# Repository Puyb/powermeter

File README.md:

Do It Yourself (DIY) Cycle Power Meter

Based on https://gitlab.com/tbressers/power/ with a custom PCB in the hardware folder

---

Original README:

This is the code for a crank-based power meter, transmitting over BLE to a bike computer. The whole project is based on Steve Jarvis website/gitlab with a nice set of improvements (see gitlab link below) and tested on a 'Adafruit Bluefruit nRF52840 Feather Express' board.

Please find the complete DIY work-instruction here:

https://gitlab.com/tbressers/power/-/wikis/home

Best regards,
Thijs

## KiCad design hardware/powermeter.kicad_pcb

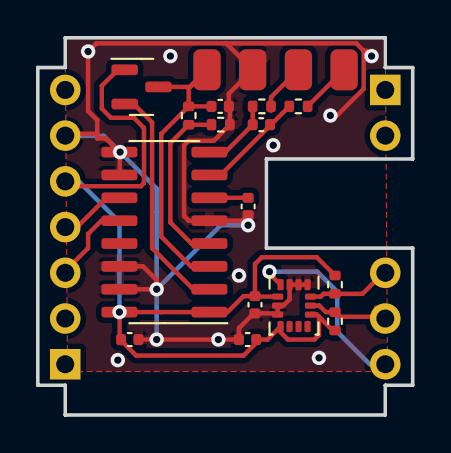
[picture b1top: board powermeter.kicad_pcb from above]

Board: 2 copper layers, 20.8 x 21.0 mm, 19 parts (1 on the bottom side), 20 nets.

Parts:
C1, C2, C5, C6: 0.1uF; C_0402_1005Metric
C3, C4: 10uF; C_0402_1005Metric
J1: Conn_01x04; connecteur
J2, J3: Conn_01x07; PinHeader_1x07_P2.54mm_Vertical
Q1: S8550; SOT-23
R1, R6: 100; R_0402_1005Metric
R2: 20k; R_0402_1005Metric
R3: 8.2k; R_0402_1005Metric
R4, R5: 10k; R_0402_1005Metric
U1: XIAO BLE; MOUDLE16P-SMD-2.54-21X17.8MM
U2: HX711; SOP-16_3.9x9.9mm_P1.27mm
U3: LSM6DS3; LGA-14_3x2.5mm_P0.5mm_LayoutBorder3x4y

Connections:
+3.3V: C3.1, C5.2, C6.1, J3.5, Q1.1 (E), R4.1, R5.1, U1.12 (3v3), U2.1 (VSUP), U2.16 (DVDD), U3.5 (VDDIO), U3.8 (VDD), U3.12 (CS)
/5V: J3.7, U1.14 (5v)
/HX_CLK: J3.4, U1.11 (D10/MOSI), U2.11 (PD_SCK)
/HX_DATA: J3.3, U1.10 (D9/MISO), U2.12 (DOUT)
/MPU_INT: J2.7, U1.7 (D6/TX), U3.4 (INT1)
/SCL: J2.6, R5.2, U1.6 (D5/A5/SCL), U3.13 (SCL)
/SDA: J2.5, R4.2, U1.5 (D4/A4/SDA), U3.14 (SDA)
GND: C2.2, C3.2, C4.2, C5.1, C6.2, J1.2, J3.6, R3.2, U1.13 (GND), U2.5 (AGND), U2.9 (INB-), U2.10 (INB+), U2.14 (XI), U2.15 (RATE), U3.1 (SDO/SA0), U3.2 (SDX), U3.3 (SCX), U3.6 (GND), U3.7 (GND)
unnamed: C4.1, J1.1, Q1.3 (C), R2.1, U2.3 (AVDD)
unnamed: J1.3, R1.2
unnamed: J1.4, R6.2
unnamed: J2.1, U1.1 (D0/A0)
unnamed: J2.2, U1.2 (D1/A1)
unnamed: J3.1, U1.8 (D7/RX)
unnamed: J3.2, U1.9 (D8/SCK)
unnamed: Q1.2 (B), U2.2 (BASE)
unnamed: C1.1, R1.1, U2.8 (INA+)
unnamed: C1.2, R6.1, U2.7 (INA-)
unnamed: C2.1, U2.6 (VBG)
unnamed: R2.2, R3.1, U2.4 (VFB)

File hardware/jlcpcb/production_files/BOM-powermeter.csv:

Comment,Designator,Footprint,LCSC
S8550,Q1,SOT-23,C105432
0.1uF,"C1,C2,C5,C6",C_0402_1005Metric,C1525
10uF,"C3,C4",C_0402_1005Metric,C15525
100,"R1,R6",R_0402_1005Metric,C25076
10k,"R4,R5",R_0402_1005Metric,C25744
20k,R2,R_0402_1005Metric,C25765
8.2k,R3,R_0402_1005Metric,C2906967
HX711,U2,SOP-16_3.9x9.9mm_P1.27mm,C6705483
LSM6DS3,U3,LGA-14_3x2.5mm_P0.5mm_LayoutBorder3x4y,C967633

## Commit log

2021-11-05 Initial commit, copied files from Steve Jarvis and added sleep mode for Feather Express boards https://iamteapot.dev/homemade-power-meter/ https://gitlab.com/sjarvis/powermeter
    TODO:
    - Cleanup code
    - Integrate calibration
    - Many more things!
2021-11-05 Cleanup
2021-11-12 Added sleep and wake-up, and started the semi- automatic calibration implementation
2021-11-12 Sleep / wake-up and semi-automatic calibration
2021-11-12 Upgrade to latest Adafruit nRF52 version
2021-11-16 Upgrade to latest board and library versions
2021-11-19 Calibration via bluetooth (Bluefruit LE connect App)
2021-11-20 Welcome message over bluetooth
2021-11-20 Update updates
2021-11-21 Added storage of calibration factor in UICR on nRF52840 (feather)
2021-11-26 Fixed calibration saving to nvram (flash)
2021-11-27 Fixed calculations
2021-11-30 Fixed cadence
2021-11-30 textual
2021-11-30 Cadence fix
2021-11-30 Remove logging
2021-11-30 future proof
2021-12-13 Interrupt driven load cell reading
2021-12-17 Full functioning
2021-12-17 Fixed kg to Newtons
2021-12-17 removed log
2021-12-17 Fixed battery reading
2021-12-17 Added z-tilt monitoring
2021-12-18 abs power and smart calibration
2021-12-18 Set MPU6050_RANGE_2000_DEG to enable measurement of fast pedaling
2021-12-20 Add new file
2021-12-23 Add new directory
2021-12-23 for release
2021-12-28 Valid defaults
2021-12-28 Updated dist
2021-12-28 Workaround for load-sensor calibration/read-out
2021-12-29 Calibration fix/workaround
2021-12-29 Fixed calibration values saving
2021-12-29 Fixed calibrations value saving
2021-12-30 Reworked
2021-12-30 Properly fixed x2 issue
2021-12-31 Updated measuring precision
2022-01-10 Improved accuracy and code-readability
2022-01-12 Fixed cadence and increased measurement robustness
2022-01-12 Added temperature and session stats
2022-01-13 Added csv session data export
2022-01-14 Changed time into delta-time
2022-01-14 Added minimum measurement time for more robust and smooth output data
2022-01-17 Sleep mode fix
2022-01-22 New measurement-algorithm to enable high-speed pedaling measurements
2022-01-22 bugfix
2022-01-23 Smoothened the force-measurements
2022-01-27 Code clean-up
2022-01-27 Gyroscope-speed based cadence measurements
2022-01-28 Fixed automatic sleep
2023-12-28 First version
2023-12-28 Fix 5v-GND short. Minor tweaks on layout
2024-01-20 Fix AD0 MPU6050 to GND
2024-01-21 Change MPU6050 to LIS6DS3TRC
2024-01-21 Move kicad files to hardware
2024-01-21 Remove orginal gitignore to simplify merge
2024-01-21 Change code to adapt to hardware
2024-01-21 Add schematics PDF and JLCPCB files
2024-01-21 Update JLCPCB files
2024-01-21 Update for LSM6DS3TRC
2024-01-21 Add datasheets
